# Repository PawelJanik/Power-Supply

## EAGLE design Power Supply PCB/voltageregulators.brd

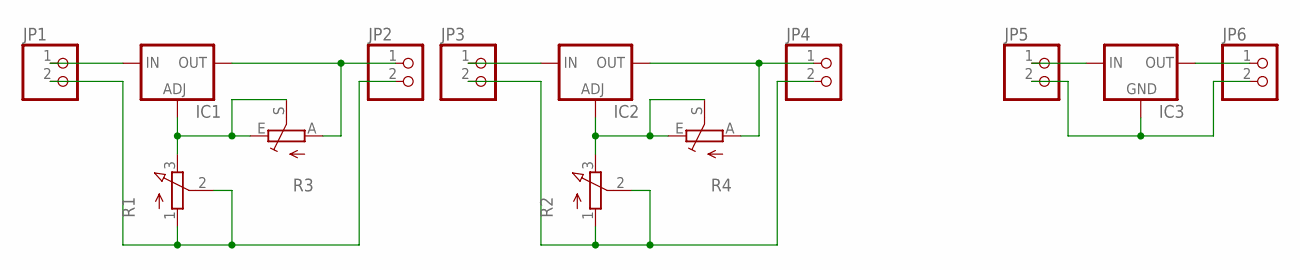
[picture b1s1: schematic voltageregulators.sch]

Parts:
IC1, IC2: LM317TS; 317TS
IC3: 78XXS
JP1, JP2, JP3, JP4, JP5, JP6: PINHD-1X2; 1X02
R1, R2: 3RP/1610N
R3, R4: TRIM_EU-LI10; LI10

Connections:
GND: JP1.2, JP2.2, R1.1 (A), R1.2 (S)
GND2: JP3.2, JP4.2, R2.1 (A), R2.2 (S)
GND3: IC3.GND, JP5.2, JP6.2
unnamed: IC3.IN, JP5.1
unnamed: IC3.OUT, JP6.1
unnamed: IC1.1 (ADJ), R1.3 (E), R3.E, R3.S
unnamed: IC1.3 (IN), JP1.1
unnamed: IC1.2 (OUT), JP2.1, R3.A
unnamed: IC2.3 (IN), JP3.1
unnamed: IC2.1 (ADJ), R2.3 (E), R4.E, R4.S
unnamed: IC2.2 (OUT), JP4.1, R4.A

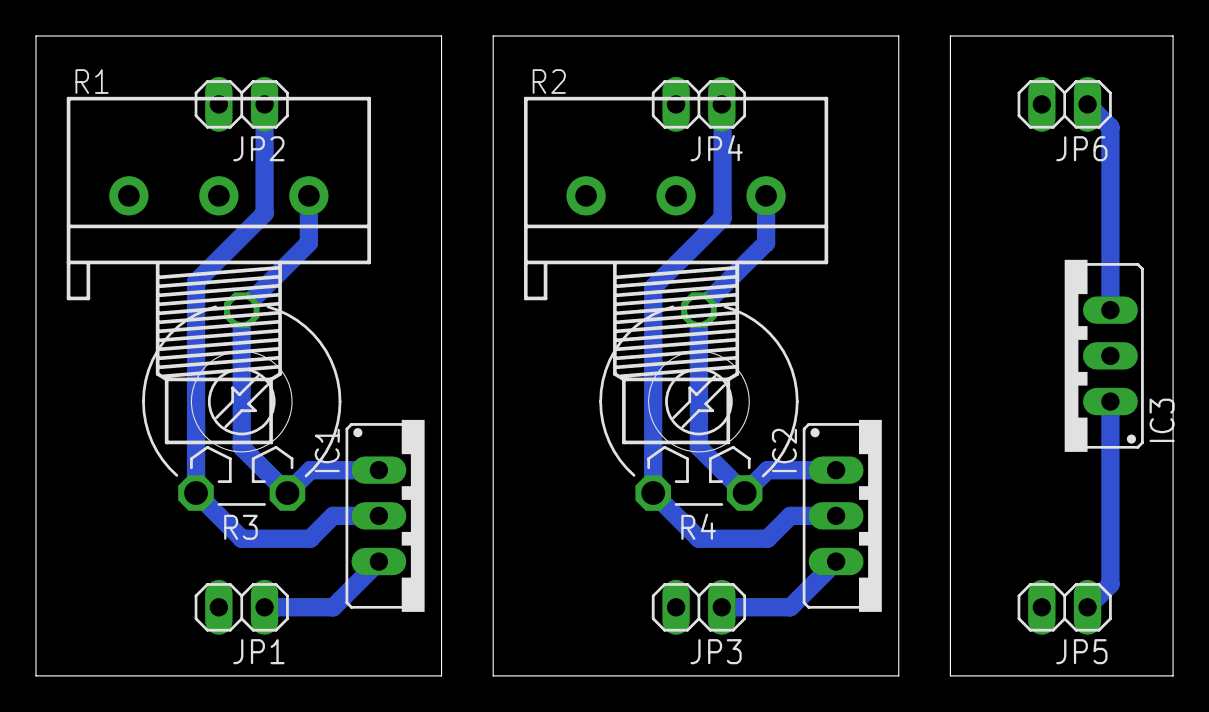
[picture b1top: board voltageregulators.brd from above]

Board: 2 copper layers, 63.2 x 35.5 mm, 13 parts (0 on the bottom side), 11 nets.

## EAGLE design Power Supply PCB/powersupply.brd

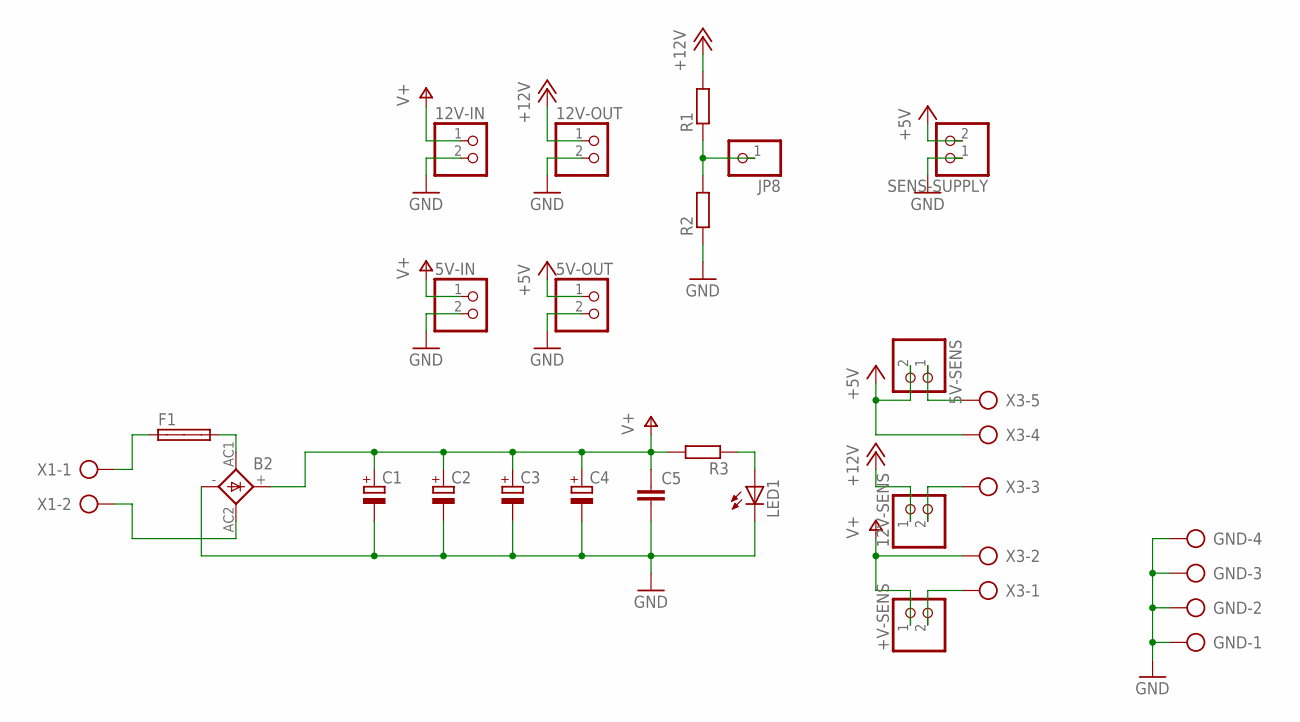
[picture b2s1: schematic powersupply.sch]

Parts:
5V-IN, 5V-OUT, 5V-SENS, 12V-IN, 12V-OUT, 12V-SENS: PINHD-1X2; 1X02
+V-SENS: PINHD-1X2; 1X02
B2: FB32
C1, C2, C3, C4: CPOL-EUE5-13; E5-13
C5: C-EU025-025X050; C025-025X050
F1: SHK20L
GND: AK300/4
JP8: PINHD-1X1; 1X01
LED1: LEDB152; Q62902-B152
R1, R2, R3: R-EU_R1206; R1206
SENS-SUPPLY: PINHD-1X2; 1X02
X1: AK300/2
X3: AK300/5

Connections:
12V-SENS: 12V-SENS.2, X3.3
+5V: 5V-OUT.1, 5V-SENS.2, SENS-SUPPLY.2, X3.4
+12V: 12V-OUT.1, 12V-SENS.1, R1.2
GND: 5V-IN.2, 5V-OUT.2, 12V-IN.2, 12V-OUT.2, B2.-, C1.-, C2.-, C3.-, C4.-, C5.2, GND.1, GND.2, GND.3, GND.4, LED1.K (C), R2.1, SENS-SUPPLY.1
unnamed: F1.1A, X1.1
unnamed: B2.AC1, F1.2A
unnamed: B2.AC2, X1.2
unnamed: +V-SENS.2, X3.1
unnamed: 5V-SENS.1, X3.5
unnamed: LED1.A, R3.1
unnamed: JP8.1, R1.1, R2.2
V+: 5V-IN.1, 12V-IN.1, +V-SENS.1, B2.+, C1.+, C2.+, C3.+, C4.+, C5.1, R3.2, X3.2

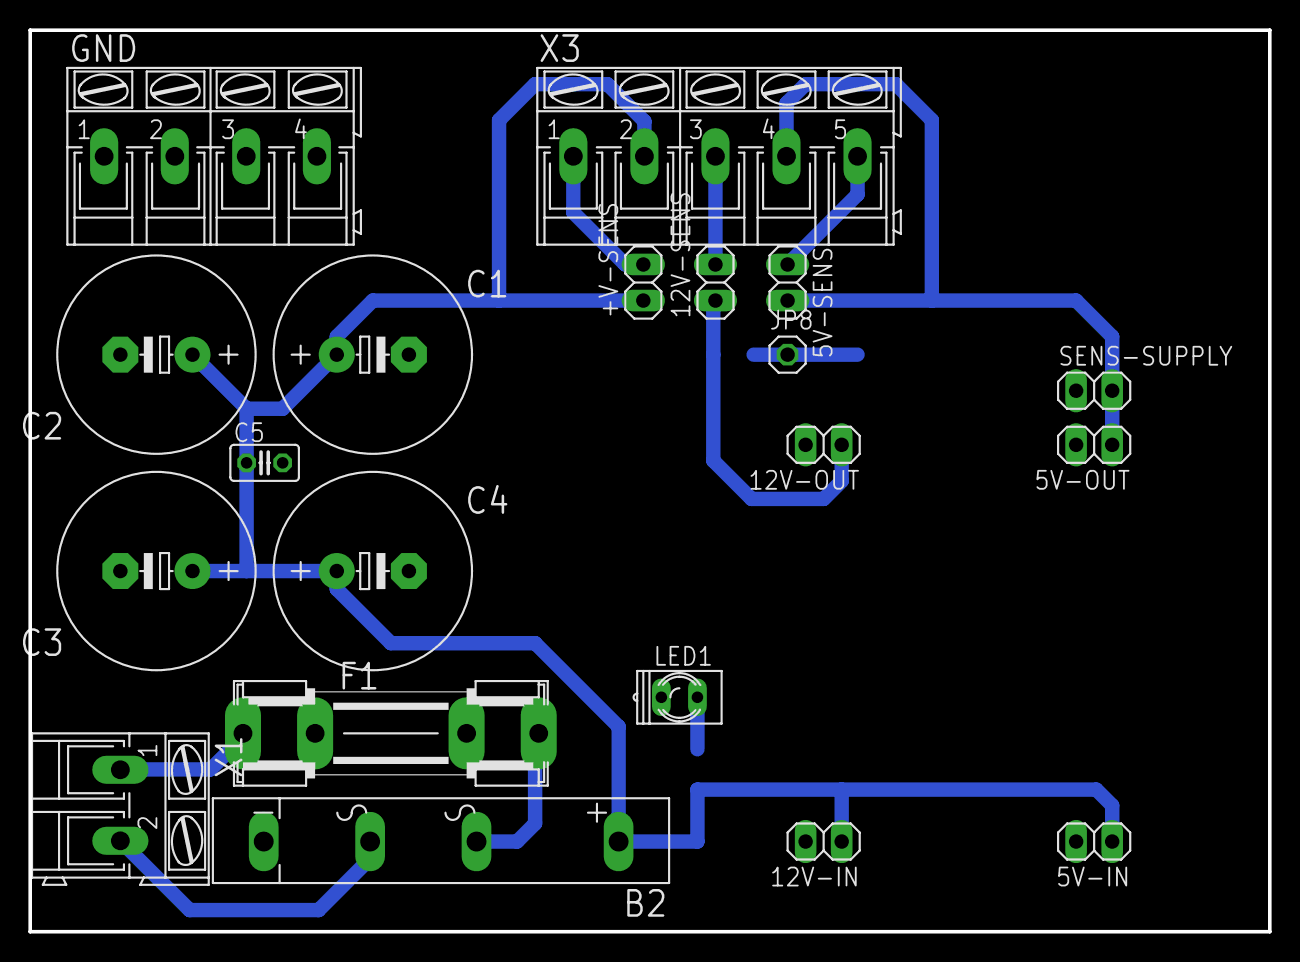
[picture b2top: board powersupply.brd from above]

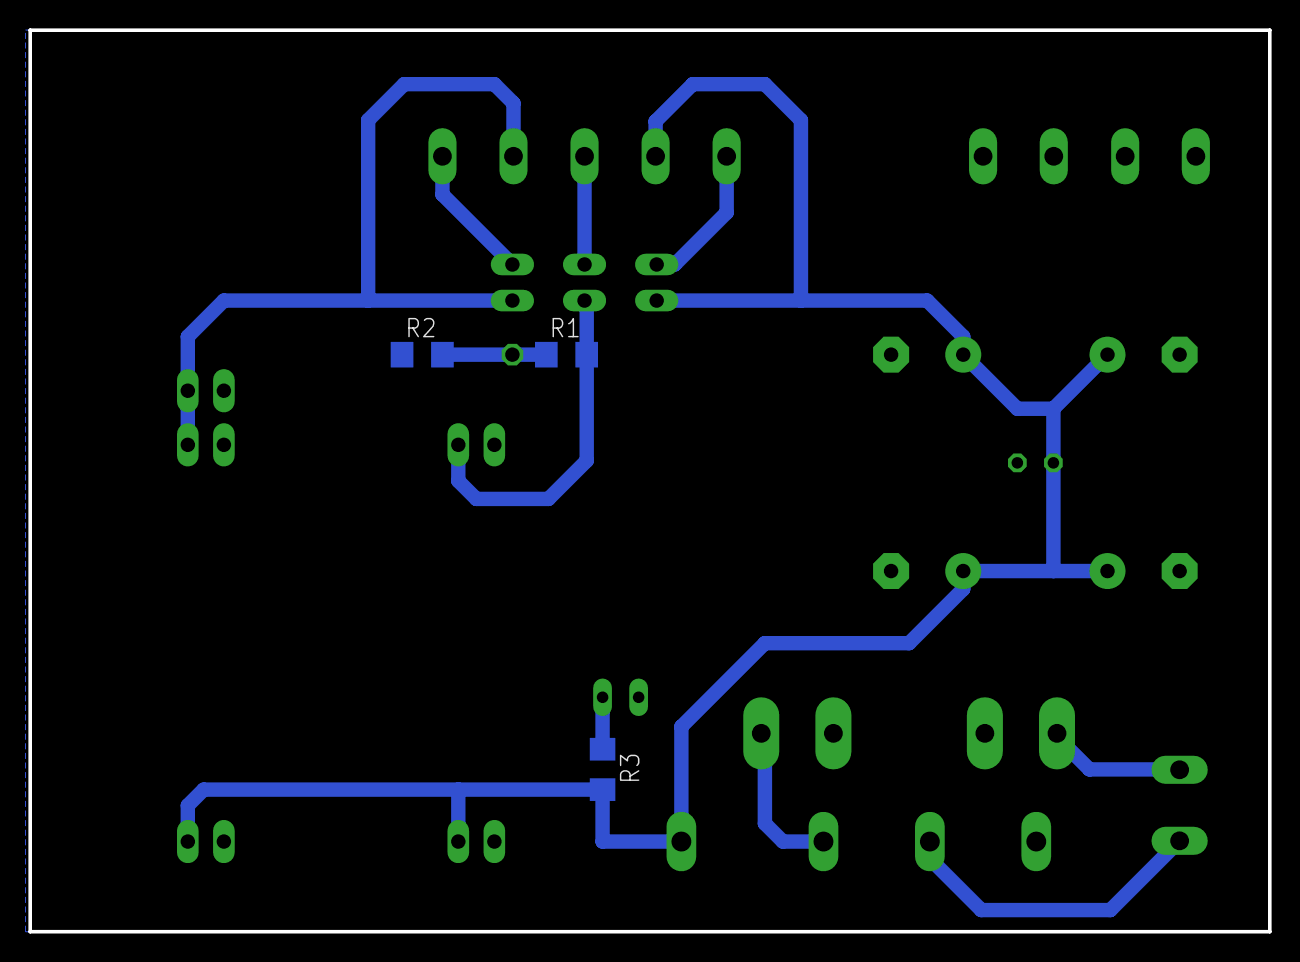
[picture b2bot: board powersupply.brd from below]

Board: 2 copper layers, 87.3 x 63.5 mm, 23 parts (3 on the bottom side), 12 nets.

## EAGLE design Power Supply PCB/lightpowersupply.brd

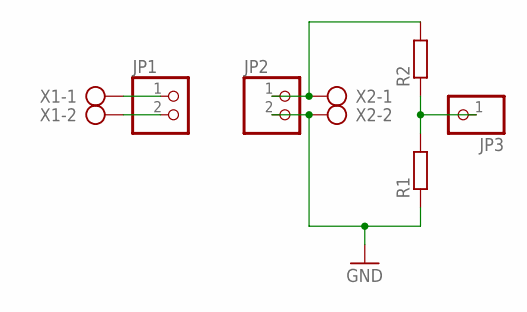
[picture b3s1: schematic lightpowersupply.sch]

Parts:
JP1, JP2: PINHD-1X2; 1X02
JP3: PINHD-1X1; 1X01
R1, R2: R-EU_R1206; R1206
X1, X2: AK300/2

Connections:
GND: JP2.2, R1.1, X2.2
unnamed: JP1.1, X1.1
unnamed: JP1.2, X1.2
unnamed: JP2.1, R2.2, X2.1
unnamed: JP3.1, R1.2, R2.1

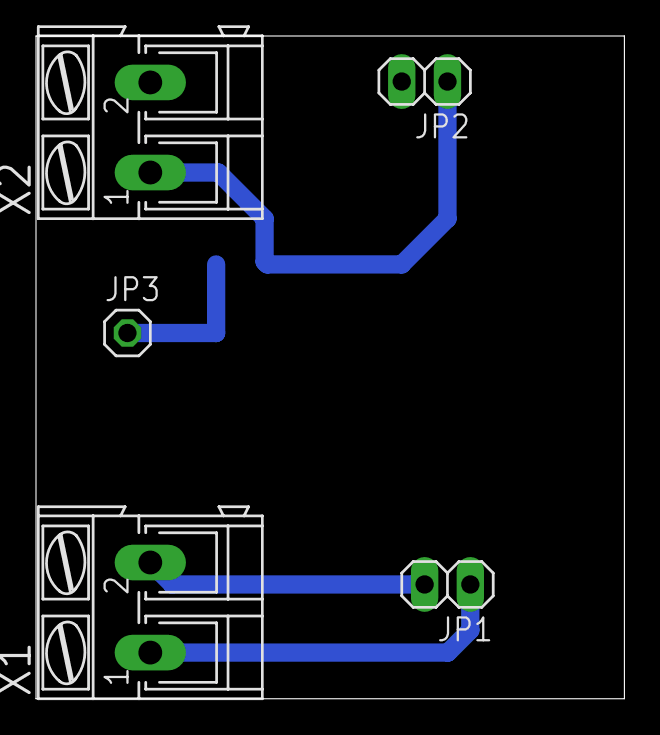
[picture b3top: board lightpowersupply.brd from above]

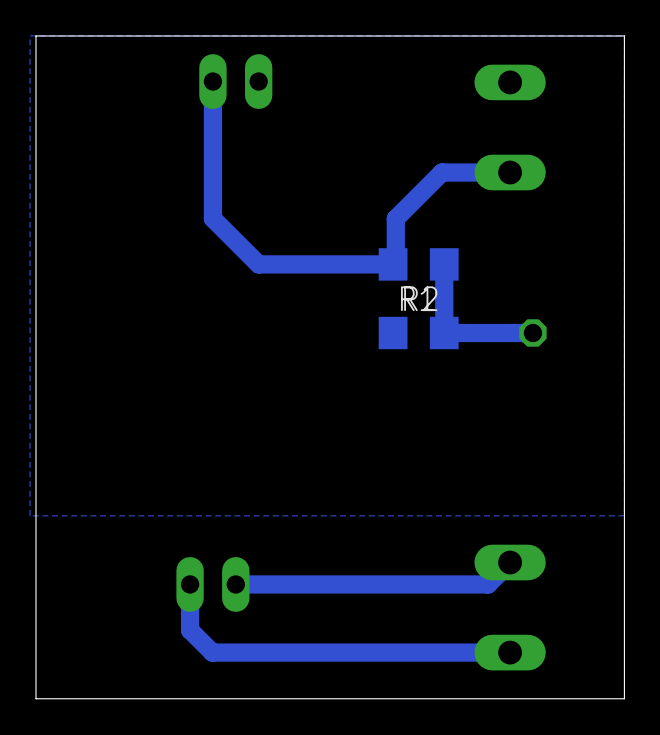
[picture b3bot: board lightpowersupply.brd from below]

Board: 2 copper layers, 32.7 x 36.8 mm, 7 parts (2 on the bottom side), 5 nets.

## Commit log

2018-04-22 Add power supply board
2018-04-23 Add light power supply board
2018-04-24 Add voltage regulator PCBs
